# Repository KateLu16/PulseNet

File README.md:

<div align="center">

# PulseNet

**Smart Wireless Quiz & Assessment System**

ESP32 clickers · BLE · Raspberry Pi gateway · FastAPI dashboard with live analytics

*An end-to-end IoT course project — Ho Chi Minh City University of Technology and Education (HCMUTE)*

</div>

---

## What is PulseNet?

PulseNet turns any classroom into an interactive one. Every student gets a
battery-powered **wireless response device**: they type their student ID on a
4×4 keypad, receive each question on a 1.8″ TFT display over BLE, and answer
with a single key press. A **Raspberry Pi** acts as the BLE gateway and local
server, running the database, REST API and the **teacher dashboard** — a web
app for importing questions, running live sessions and analyzing results in
real time.

The whole chain — custom PCB, 3D-printed enclosure, firmware, gateway,
backend, dashboard and analytics — was designed and built from scratch.

## Highlights

- **Full wireless classroom flow** — student registration (ID ↔ device MAC
  mapping), question delivery, A–D answering and acknowledgement, all over BLE
  with sequence numbers for duplicate/stale-packet protection.
- **Teacher dashboard** — 7 views: Dashboard, Question Bank, Import, Sessions,
  Devices, Live and Results, following a *Prepare → Conduct → Analyze* workflow.
- **Live monitoring** — per-question answer distribution, submitted/missing
  students and device online/offline status via gateway heartbeats, updated
  while the quiz is running.
- **Rich analytics** — student scores, correct/wrong/blank breakdown,
  per-question accuracy and full-class statistics after every session.
- **AI quiz generation** — upload a PDF (lecture notes, slides…) and Gemini
  generates a complete multiple-choice question set, with model fallback and
  retry on rate limits. Works fully offline without an API key.
- **CSV question import** — validated template upload with per-row error
  reporting, plus append/conflict handling for existing question banks.
- **Self-paced & presenter-led modes** — students may answer questions in any
  order (self-paced) or follow the teacher's current question; the backend
  owns quiz deadlines even if the gateway goes offline.
- **Custom hardware** — 2-layer PCB designed in Proteus (ESP32-WROOM-32,
  ST7735 TFT, 4×4 keypad, power terminal block) in a 3D-printed enclosure.

## Screenshots

| Prepare — import questions (CSV or AI-generated from PDF) | Conduct — live session |
|---|---|
|  |  |

| Dashboard home | Analyze — results & statistics |
|---|---|
|  |  |

## System architecture

```
Student Device (×N)          Raspberry Pi 4B                    Teacher
┌──────────────────┐   BLE  ┌──────────────────────┐   Wi-Fi  ┌───────────────┐
│ ESP32-WROOM-32   │        │ BLE gateway (bleak)  │          │ Tablet / PC   │
│ 4×4 keypad       ├───────►│  FastAPI backend     ├─────────►│ Browser       │
│ 1.8" TFT ST7735  │        │  SQLite (SQLAlchemy) │  :8000   │ Dashboard     │
│ RGB LED · CR2032 │◄───────┤  Analytics engine    │          │               │
└──────────────────┘  Q/ACK └──────────────────────┘          └───────────────┘
```

**BLE protocol** — the device exposes Nordic-UART-style GATT characteristics
for *registration*, *question*, *answer* and *ACK*. Every answer carries a
monotonic sequence number; the backend accepts only the newest answer per
(student, question) pair and detects duplicate delivery.

## Hardware

### Student device

| Subsystem | Part |
|---|---|
| MCU / radio | ESP32-WROOM-32 (Bluetooth Low Energy) |
| Display | 1.8″ TFT LCD, ST7735 driver, 160×128 |
| Input | 4×4 matrix keypad (0–9 student ID, A–D answer, `*` clear, `#` confirm) |
| Feedback | RGB status LED (idle / connecting / accepted / error) |
| Power | CR2032 coin cell + slide switch |
| Boards | Custom 2-layer PCB, 47.8 × 67.4 mm |
| EDA | Proteus Design Suite (schematic + PCB layout, `PCB.pdsprj`) |
| Enclosure | 3D-printed housing (SolidWorks design + STEP models) |

| Schematic (Proteus) | PCB layout |
|---|---|
|  |  |

### Firmware

- Built with **PlatformIO** (Arduino framework), **NimBLE-Arduino** for the
  BLE GATT server and **Adafruit GFX + ST7735** drivers.
- A compact state machine handles the full student journey — including a
  paginated document renderer so long questions scroll cleanly on the small
  TFT, and a boot splash with the university logo.

## Server

- **Backend** — Python FastAPI + SQLAlchemy over SQLite, served by uvicorn on
  port 8000. REST endpoints for quizzes, questions, devices, responses,
  monitoring and analytics.
- **BLE gateway** — Python service using [bleak](https://github.com/hbldh/bleak)
  to connect student devices, forward registrations/answers to the API and
  push questions/ACKs back out.
- **Dashboard** — dependency-free static web app (`HTML/CSS/JS`) served by the
  backend, designed for tablet browsers.
- **Database schema:**

## Repository layout

```
PulseNet/
├── PulseNet-device/     # ESP32 firmware (PlatformIO, NimBLE, Arduino)
├── PulseNet-server/     # Raspberry Pi server
│   ├── backend/         #   FastAPI app, dashboard (web/), tests, .env.example
│   └── gateway/         #   BLE gateway (bleak) + debug tools
├── PCB.pdsprj           # Proteus project — schematic + 2-layer PCB (47.8 × 67.4 mm)
├── 3D_DESIGN/           # Enclosure CAD (SolidWorks + STEP)
├── docs/img/            # Figures used by this README
└── .github/workflows/   # CI: backend tests + firmware build
```

## Quick start

### 1. Server (Raspberry Pi or any Linux/macOS box)

```bash
git clone https://github.com/KateLu16/PulseNet.git    # or copy the folder to the Pi
cd PulseNet/PulseNet-server/backend

python -m venv .venv
source .venv/bin/activate          # Windows: .venv\Scripts\activate
pip install -r requirements.txt

# Optional — enable AI quiz generation (https://aistudio.google.com/apikey)
cp .env.example .env               # then edit GEMINI_API_KEY=...

python -m uvicorn app.main:app --host 0.0.0.0 --port 8000
```

Open `http://<server-ip>:8000/` in a browser — that's the teacher dashboard.
The BLE gateway additionally needs `pip install bleak`; on the Pi the
ready-made scripts in `PulseNet-server/` (`start_server.sh`, `start_gateway.sh`,
`status_all.sh`, `stop_all.sh`) manage both services.

### 2. Student device firmware

```bash
pip install platformio
pio run -d PulseNet-device -t upload    # build + flash over USB
pio device monitor -d PulseNet-device   # 115200 baud serial monitor
```

On first boot the device shows a splash screen, then waits for the student ID.

## Testing

The backend ships with a hardware-free integration suite that simulates a
full classroom session — three devices, self-paced answers, duplicate/stale
packets, re-answers, deadlines and result aggregation — against a throwaway
database:

```bash
cd PulseNet-server/backend
python test_integration_e2e.py
```

This is the same suite that runs in CI on every push.

## Roadmap

- [ ] RGB LED status patterns & battery-voltage monitoring on the device
- [ ] Larger multi-device stress test (10+ concurrent clickers)
- [ ] Enclosure revision 2 with better keypad feel
- [ ] Export results to Excel/CSV reports

## Author

**Luu Khac Thao Trang** ([@KateLu16](https://github.com/KateLu16))<br>
Robotics & Artificial Intelligence — Faculty of Mechanical Engineering<br>
Ho Chi Minh City University of Technology and Education (HCMUTE)

## License

Released under the [MIT License](LICENSE).

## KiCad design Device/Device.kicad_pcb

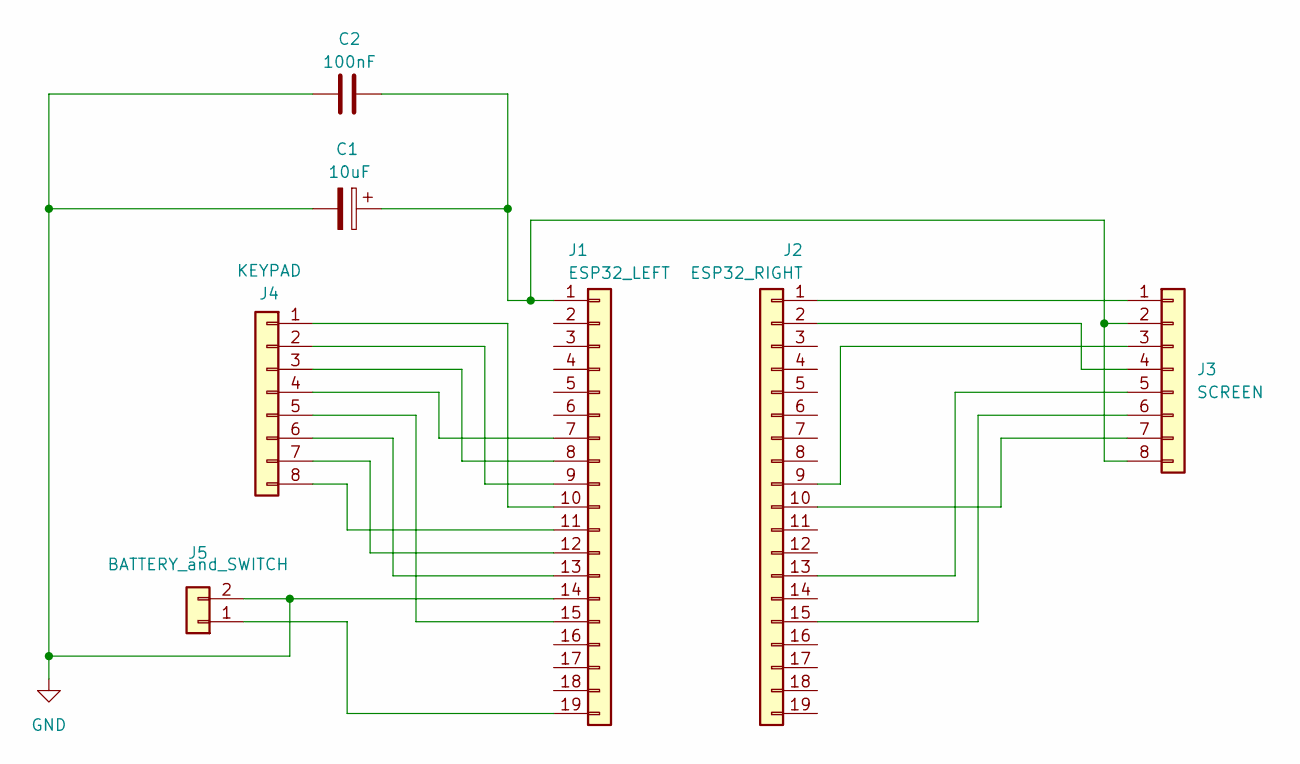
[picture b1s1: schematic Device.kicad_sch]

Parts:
C1: 10uF; CP_Radial_D4.0mm_P2.00mm
C2: 100nF; C_Disc_D3.4mm_W2.1mm_P2.50mm
J1: ESP32_LEFT; PinSocket_1x19_P2.54mm_Vertical
J2: ESP32_RIGHT; PinSocket_1x19_P2.54mm_Vertical
J3: SCREEN; PinSocket_1x08_P2.54mm_Vertical
J4: KEYPAD; PinSocket_1x08_P2.54mm_Vertical
J5: BATTERY_and_SWITCH; TerminalBlock_MaiXu_MX126-5.0-02P_1x02_P5.00mm

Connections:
GND: C1.2, C2.1, J1.14, J5.2
unnamed: C1.1, C2.2, J1.1, J3.2, J3.8
unnamed: J1.7, J4.4
unnamed: J1.8, J4.3
unnamed: J1.9, J4.2
unnamed: J1.10, J4.1
unnamed: J1.11, J4.8
unnamed: J1.12, J4.7
unnamed: J1.13, J4.6
unnamed: J1.15, J4.5
unnamed: J1.19, J5.1
unnamed: J2.1, J3.1
unnamed: J2.2, J3.4
unnamed: J2.9, J3.3
unnamed: J2.10, J3.7
unnamed: J2.13, J3.5
unnamed: J2.15, J3.6

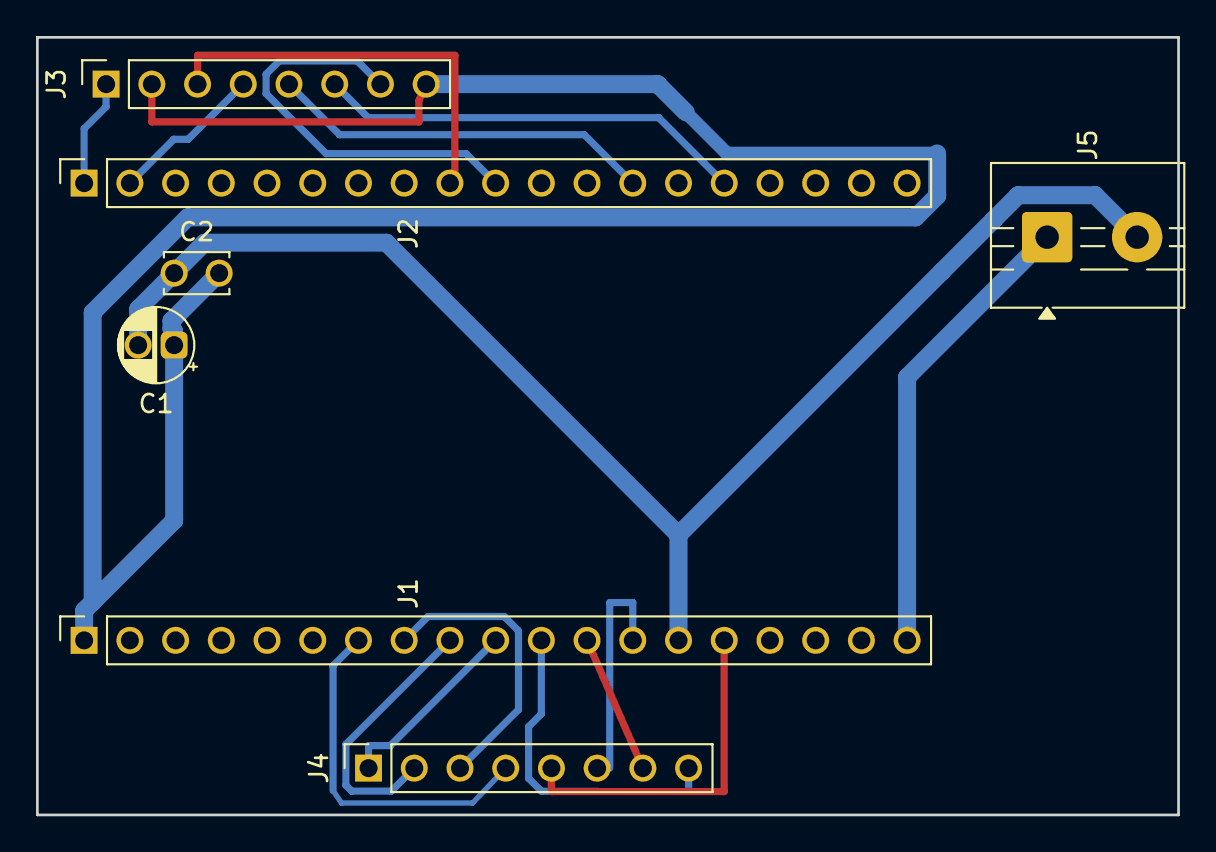
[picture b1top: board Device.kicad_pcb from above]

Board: 2 copper layers, 63.4 x 43.2 mm, 7 parts (0 on the bottom side), 17 nets.

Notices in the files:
README.md:
License: MIT
